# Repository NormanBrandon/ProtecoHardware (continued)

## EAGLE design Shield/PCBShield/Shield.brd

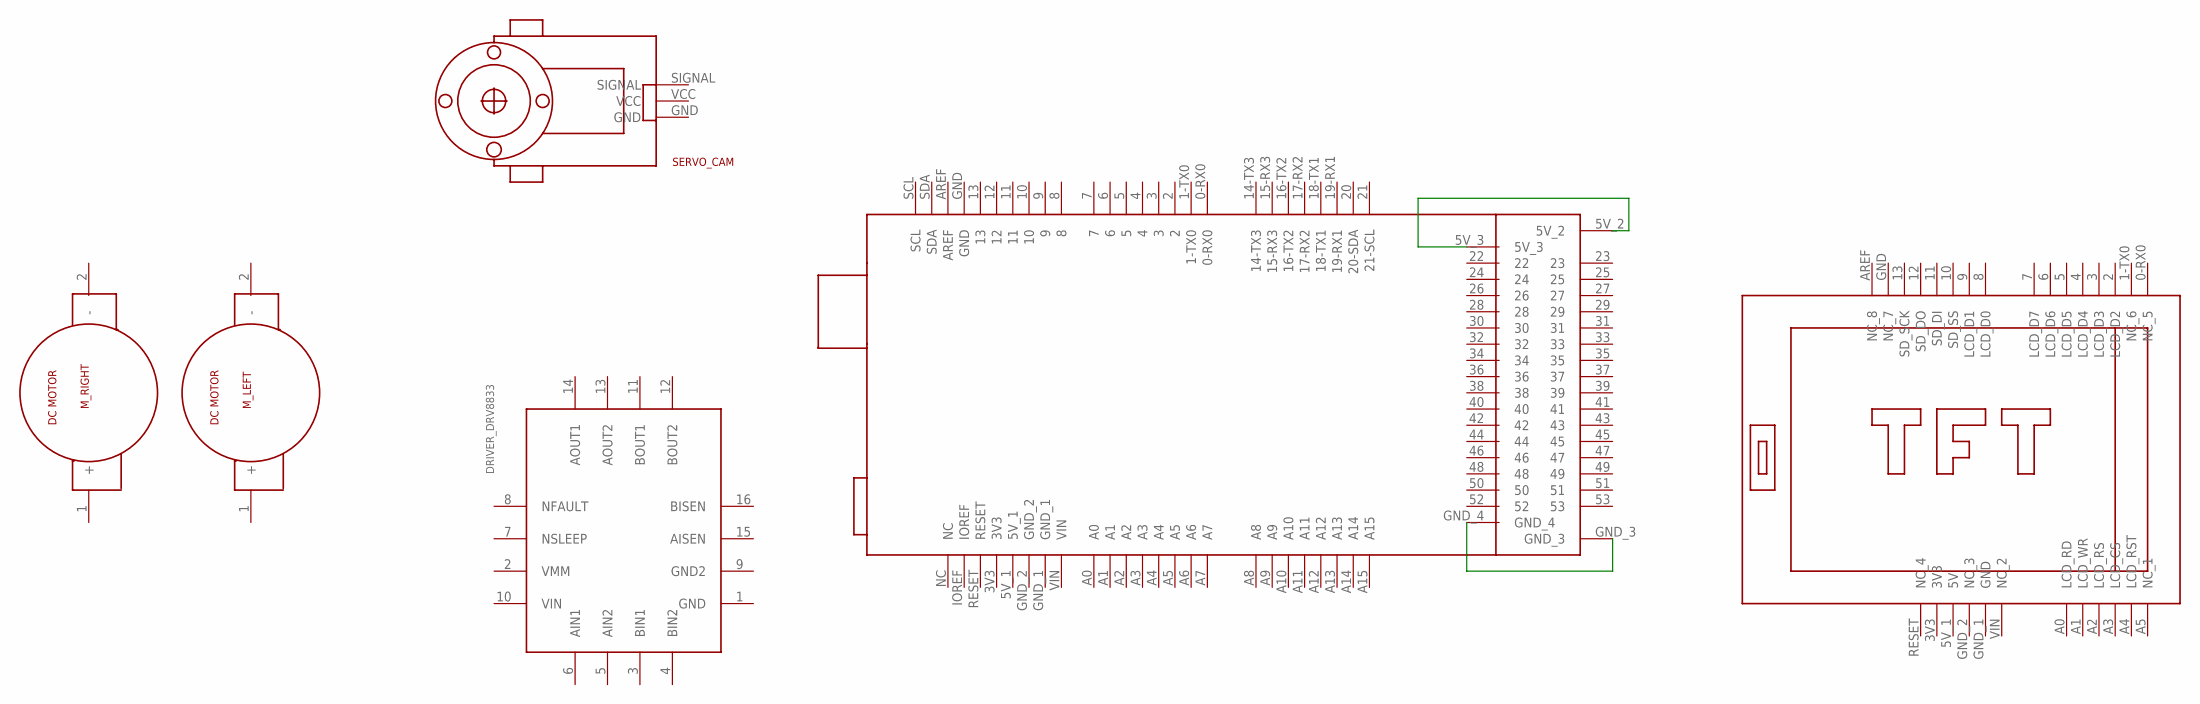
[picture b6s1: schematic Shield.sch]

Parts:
DRIVER_DRV8833: MODULO
M_LEFT: OUTPUTMALE; OUPUTMALE
M_RIGHT: OUTPUTMALE; OUPUTMALE
SERVO_CAM: SERVOMOTORES; SERVO
TFT-ARDUINO-MEGA: TFT_ARDUINO-UNO-MEGA; TFT-ARDUINO-UNO-MEGA
U$1: ARDUINO_MEGA; ARDUINO-MEGA

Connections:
unnamed: U$1.5V_2, U$1.5V_3
unnamed: U$1.GND_3, U$1.GND_4

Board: 2 copper layers, 6 parts (0 on the bottom side), 2 nets, no tracks yet.

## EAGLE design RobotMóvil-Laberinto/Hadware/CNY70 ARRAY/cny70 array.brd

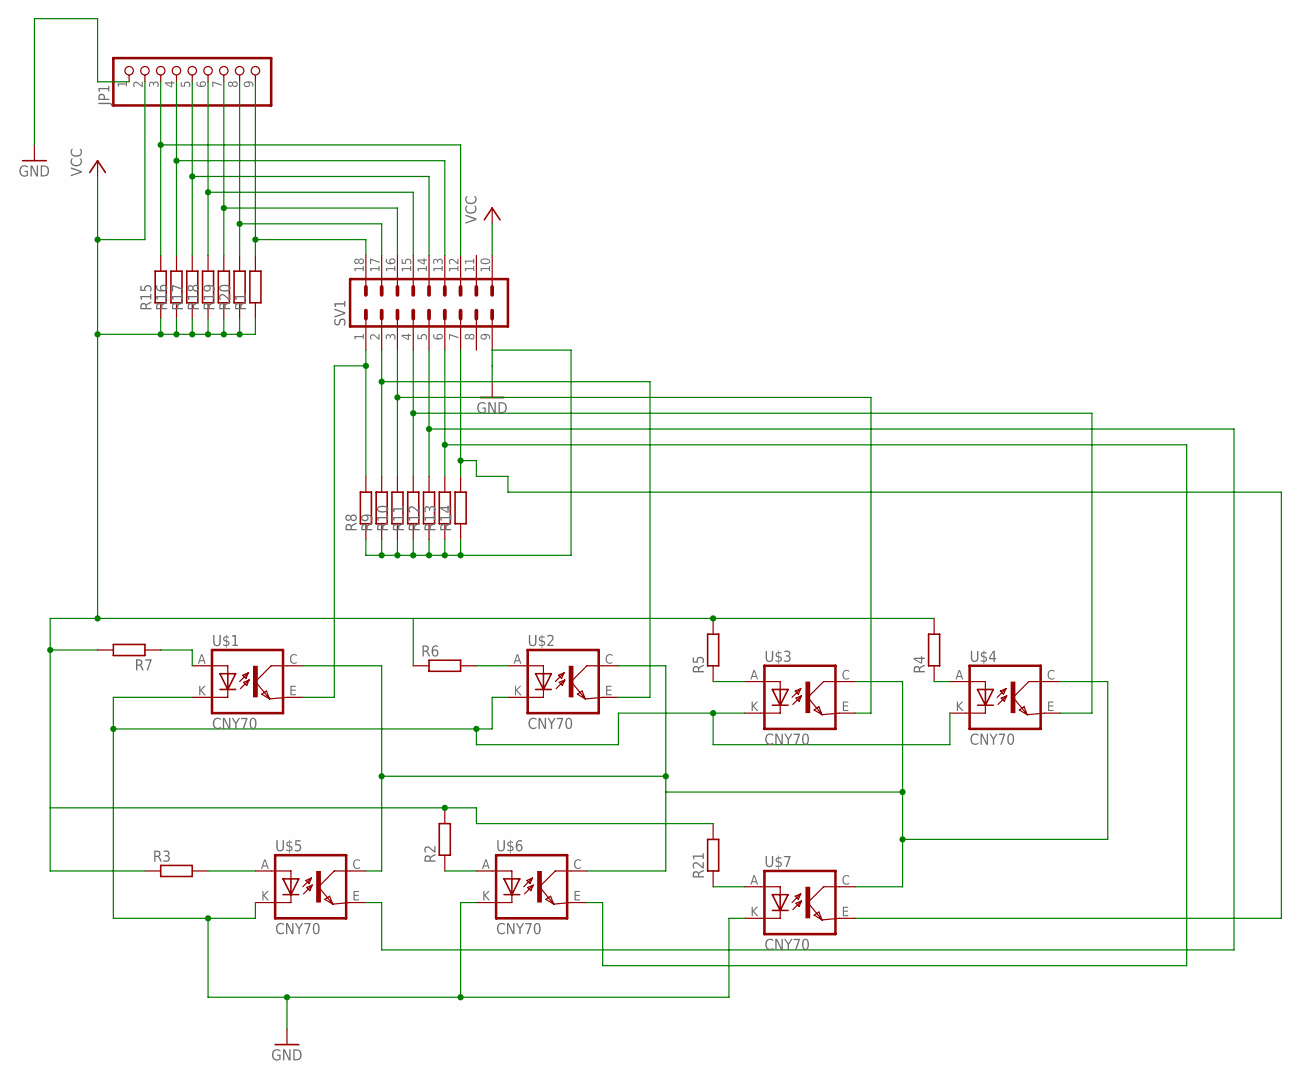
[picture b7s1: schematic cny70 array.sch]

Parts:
JP1: PINHD-1X9; 1X09
R1, R2, R3, R4, R5, R6, R7, R8, R9, R10, R11, R12, R13, R14, R15, R16, R17, R18, R19, R20, R21: R-EU_0204/5; 0204/5
SV1: IC18PL
U$1, U$2, U$3, U$4, U$5, U$6, U$7: CNY70; 4

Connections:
GND: JP1.1, R8.1, R9.1, R10.1, R11.1, R12.1, R13.1, R14.1, SV1.9, U$1.K (C), U$2.K (C), U$3.K (C), U$4.K (C), U$5.K (C), U$6.K (C), U$7.K (C)
unnamed: JP1.3, R15.2, SV1.12
unnamed: JP1.4, R16.2, SV1.13
unnamed: JP1.5, R17.2, SV1.14
unnamed: JP1.6, R18.2, SV1.15
unnamed: JP1.7, R19.2, SV1.16
unnamed: JP1.8, R20.2, SV1.17
unnamed: R8.2, SV1.1, U$1.E (EMI)
unnamed: R9.2, SV1.2, U$2.E (EMI)
unnamed: R10.2, SV1.3, U$3.E (EMI)
unnamed: R11.2, SV1.4, U$4.E (EMI)
unnamed: R12.2, SV1.5, U$5.E (EMI)
unnamed: R13.2, SV1.6, U$6.E (EMI)
unnamed: R14.2, SV1.7, U$7.E (EMI)
unnamed: R2.1, U$6.A
unnamed: R21.1, U$7.A
unnamed: U$1.C (COL), U$2.C (COL), U$3.C (COL), U$4.C (COL), U$5.C (COL), U$6.C (COL), U$7.C (COL)
unnamed: R4.1, U$4.A
unnamed: R5.1, U$3.A
unnamed: R6.2, U$2.A
unnamed: R7.1, U$1.A
unnamed: R3.2, U$5.A
unnamed: JP1.9, R1.2, SV1.18
VCC: JP1.2, R1.1, R2.2, R3.1, R4.2, R5.2, R6.1, R7.2, R15.1, R16.1, R17.1, R18.1, R19.1, R20.1, R21.2, SV1.10

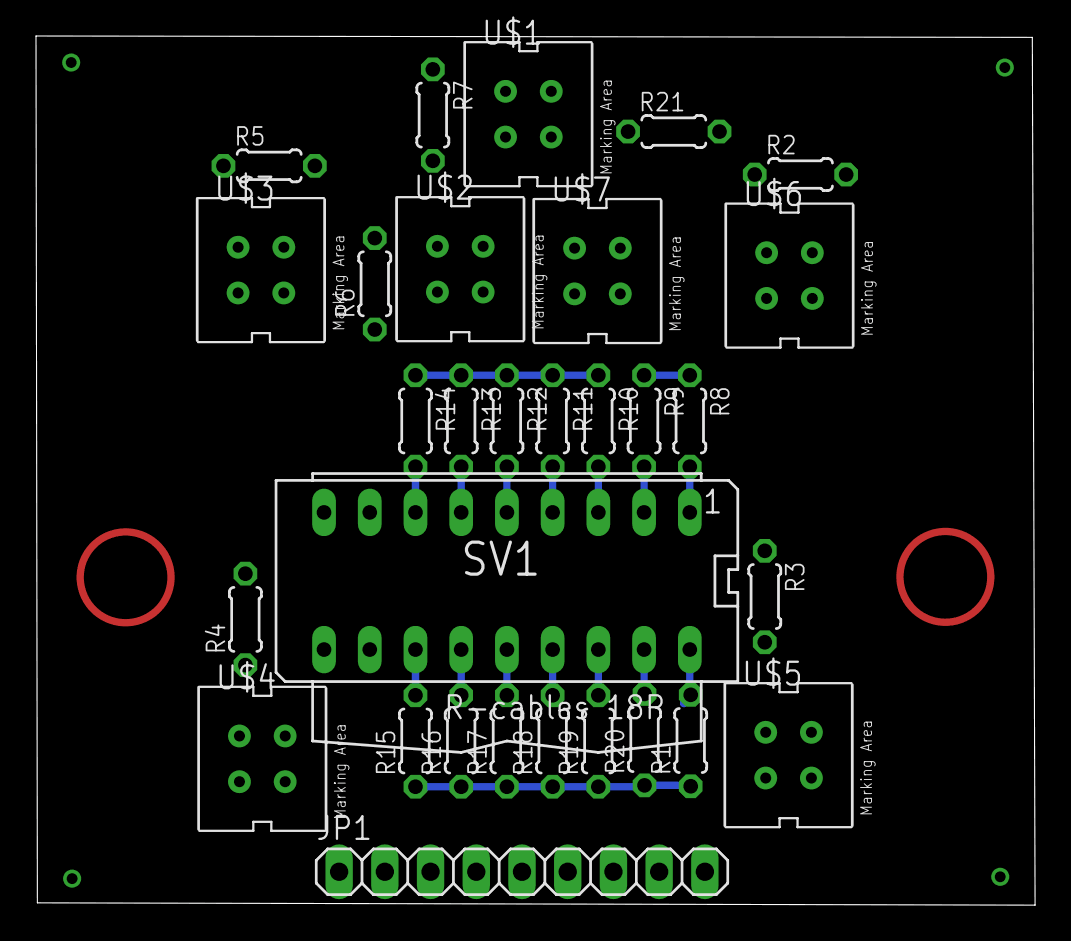
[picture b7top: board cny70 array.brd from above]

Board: 2 copper layers, 55.5 x 48.3 mm, 30 parts (0 on the bottom side), 24 nets.

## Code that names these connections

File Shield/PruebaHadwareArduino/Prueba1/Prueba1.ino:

/*#include <VarSpeedServo.h>
VarSpeedServo servoBase;
VarSpeedServo servoAng;
VarSpeedServo servo3;
VarSpeedServo servo4;*/
/*Definicion de Pines*/
byte led1 = 27, led2 = 29,led3 = 31,led4 = 33;
int infraLeft = A5, infraMidd = A6, infraRight= A7;
byte sg901 = 37, sg902 = 39, sg903 = 41, sg904 = 43;
byte dip1 = 23, dip2 = 22, dip3 = 26 ,dip4 = 24;
byte push = 25;
byte led1w = 45;
byte buzzer = 35;
int m_left_pwm = 44 , m_right_pwm = 46, m_left1 = 30 ,m_left2 = 28, m_right1 = 32 ,m_right2 = 34;
int enc_right1 = 18 ,enc_right2 = A8, enc_left1 = 14 ,enc_left2 = 15;  
byte SF = 48, SCI = 47, SSI = 49, SCD =50 ,SII = 51,SSD = 52 ,SID = 53; 

void setup() {
/*  servoBase.attach(sg901);
  servoAng.attach(sg902);
  servo3.attach(sg903);
  servo4.attach(sg904);*/
  Serial.begin(9600);
  pinMode(led1,OUTPUT);
  pinMode(led2,OUTPUT);
  pinMode(led3,OUTPUT);
  pinMode(led4,OUTPUT);
  pinMode(buzzer,OUTPUT);
  pinMode(led1w,OUTPUT);
  pinMode(dip1,INPUT);
  pinMode(dip2,INPUT);
  pinMode(dip3,INPUT);
  pinMode(dip4,INPUT);
  pinMode(push,INPUT);

  pinMode(m_left_pwm,OUTPUT);
  pinMode(m_right_pwm,OUTPUT);
  pinMode(m_left1,OUTPUT);
  pinMode(m_right1,OUTPUT);
  pinMode(m_left2,OUTPUT);
  pinMode(m_right2,OUTPUT);
  pinMode(infraLeft,INPUT);
  pinMode(infraMidd,INPUT);
  pinMode(infraRight,INPUT);   
  pinMode(SF,INPUT);
  pinMode(SCI,INPUT);
  pinMode(SSI,INPUT);
  pinMode(SCD,INPUT);
  pinMode(SII,INPUT);
  pinMode(SSD,INPUT);
  pinMode(SID,INPUT);

   
}

void loop() {
  
  long tiempo=millis(); //tiempo antes de iniciar la lectura
  int D_cm=distancia(20,infraLeft); //lectura de distancia
  tiempo=millis()-tiempo; //milisegundos que duró la lectura
  Serial.print("Tiempo de lectura: ");
  Serial.print(tiempo); 
  Serial.print("ms  Distancia: ");
  Serial.print(D_cm);
  Serial.println("  cm");
  delay(100);
  adelante();
  
}


void adelante(){
  analogWrite(m_left_pwm,255);
  analogWrite(m_right_pwm,255);
  digitalWrite(m_left1,HIGH);
  digitalWrite(m_left2,LOW);
  digitalWrite(m_right1,HIGH);
  digitalWrite(m_right2,LOW);
  }
void atras(){
  analogWrite(m_left_pwm,255);
  analogWrite(m_right_pwm,255);
  
  digitalWrite(m_left1,LOW);
  digitalWrite(m_left2,HIGH);
  digitalWrite(m_right1,LOW);
  digitalWrite(m_right2,HIGH);
  }
float distancia(int n,int pin)
{
  long suma=0;
  for(int i=0;i<n;i++)
  {
    suma=suma+analogRead(pin);
  }  
  float adc=suma/n;
  //float distancia_cm = 340.2736 * pow(adc, -0.5346);//1-a
    float distancia_cm = 1584.7294 * pow(adc, -0.9205) + 1;//1-b-mejor
    //float distancia_cm = 3476.457289 * pow(adc, -1.048674);//2-a-mejor
   // float distancia_cm = 2109.491608 * pow(adc, -0.966424);//3-a-mejor

  return(distancia_cm);
}

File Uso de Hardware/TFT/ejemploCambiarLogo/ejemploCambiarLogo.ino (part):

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#define YM 7
#define XP 6

#define LCD_CS A3
#define LCD_CD A2
#define LCD_WR A1
#define LCD_RD A0
#define SD_SS 10
#define LCD_RESET A4

#define PRESION_MIN 10
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  Serial.begin(9600); //Usaremos el monitor serial para detectar posibles errores o ver que todo marche bien
  tft.reset(); //Reseteamos e iniciamos comunicación con la TFT
  tft.begin(0x9341); //Iniciamos indicando el controlador correspondiente
  pinMode(SD_SS, OUTPUT); //Declaramos el pin SD_SS como de salida
  Serial.print(F("Iniciando tarjeta SD..."));
  if (!SD.begin(SD_SS)) { //begin instanciará la SD. Si todo sale bien arrojará un true, en otro caso, un false
    Serial.println("Fallido");
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
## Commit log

2019-03-23 Recursos iniciales
2019-03-23 Agregando PCBs
2019-03-30 Mejorando y agregando librerias
2019-03-31 Avance en Shield
2019-04-02 Avance shield y correccion librerias
2019-04-04 Se agrega carpeta del diseño mecánico del Robot. Se añaden diseños de Raspberry y Chasis
2019-04-05 probando :v
2019-04-05 probando x2
2019-04-05 Camara Arduino
2019-04-05 Control de robot via Wifi (Arduino)
2019-04-05 Robot con Camara controlado por Wifi
2019-04-05 detallitos :grin:
2019-04-05 Avance Shield
2019-04-07 Programacion Inalambrica con BT
2019-04-08 Más avance
2019-04-09 Name
2019-04-09 Conexiones
2019-04-09 Conexiones+
2019-04-09 Add Pin Disposition
2019-04-10 Se agregan elementos del diseño mecánico
2019-04-11 Disposicion de pines
2019-04-11 Preruteo
2019-04-11 Ruteo
2019-04-12 Ruteo avance
2019-04-12 Avance del abstract.
2019-04-12 Creación de manual de arduino desde la terminal de linux
    Se agrego una guía básica con los comandos necesarios para poder controlar arduino desde la terminal de linux sin la necesidad de la IDE de Arduino
2019-04-12 More Route
2019-04-13 Ruote Finish
2019-04-13 Ruteo Ajustes
2019-04-15 Retoques
2019-04-17 Shield Terminada
2019-04-22 Objtivo
2019-04-22 Sketch de la base terminado. Faltan extrusiones y otros detalles.
2019-04-22 Agregados los detalles correspondientes a puerto USB y puerto de alimentación. Se agregaron cotas.
2019-04-29 Sobre robótica
2019-05-04 Primer Programa de Pruebas
2019-07-04 Cambios
2019-07-14 Casitillin
2019-07-25 Diseño Mecanico, avance significativo
2019-08-14 Impresion MDF
2019-08-17 Creacion apartado para manuales de uso del Hardware. Creacion archivo ManualTFT
2019-08-17 Primer propuesta de video :purple_heart:
2019-08-18 pausa tecnica por una surprise party :v
2019-08-18 Segunda Propuesta :trollface:
2019-08-19 Manual de ML
2019-08-19 Manual Machine Learning
2019-08-23 Creación del archivo del sensor MPU6050
    Se creo el archivo y se añadió la introducción
2019-08-23 Rename Sensor MPU6050.md to SensorMPU6050.md
2019-08-24 Reestructura carpeta Uso de Hardware, actualización de Manual TFT
2019-08-25 Create Sensor de distancia.md
    Caracterización del sensor de distancia SHARP
2019-08-25 Carpeta del sensor
2019-08-25 borra
2019-09-01 Update ManualTFT
2019-09-17 Update ManualTFT; ejemplo SD; imágenes
2019-09-25 nuevo ejemplo con TFT
2019-09-25 Código para obtener valores de caracterización
2019-09-25 Código para medir distancias
    vienen caracterización de los tres sensores del robot
2019-09-26 update TFT/
2019-09-27 Sensor Reflectivo
